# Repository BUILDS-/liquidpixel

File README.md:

# LiquidPixels

A project of [Christopher Woodall](http://www.cjwoodall.com) and 
[BUILDS](http://www.builds.cc).

## Rev. A Logs

- 4 proven working, 5 broked... Not 100% sure why, doesn't seem to be a soldering issue. I could have hooked them up wrong somehow during testing, but this should only apply to 1 or 2.
- Holes for .1" spaced headers are a little small, widen for future revisions.

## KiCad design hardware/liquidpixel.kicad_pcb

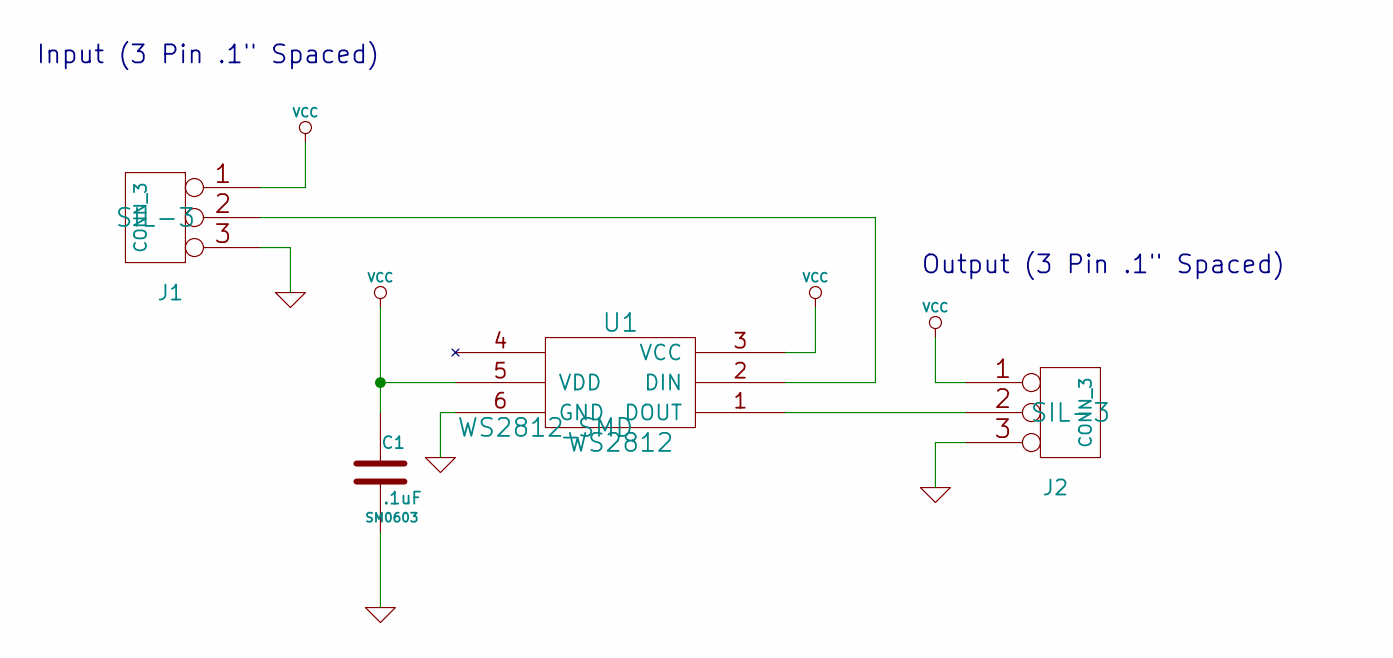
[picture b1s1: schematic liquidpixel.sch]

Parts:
C1: .1uF; SM0603
J1, J2: CONN_3; SIL-3
U1: WS2812; WS2812_SMD

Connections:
GND: C1.2, J1.3, J2.3, U1.6 (GND)
unnamed: J1.2 (PM), U1.2 (DIN)
unnamed: J2.2 (PM), U1.1 (DOUT)
VCC: C1.1, J1.1, J2.1, U1.3 (VCC), U1.5 (VDD)

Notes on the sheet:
Input (3 Pin .1" Spaced)
Output (3 Pin .1" Spaced)

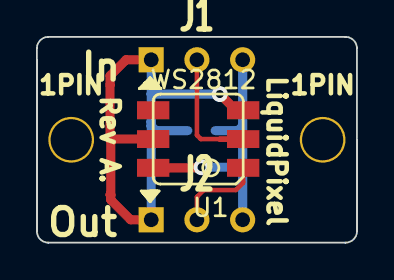
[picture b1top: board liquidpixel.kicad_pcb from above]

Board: 2 copper layers, 17.8 x 11.4 mm, 6 parts (1 on the bottom side), 4 nets.

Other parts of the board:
1PIN, 1PIN#2: P***; 1pin

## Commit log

2013-10-24 starting
2013-10-24 Added git ignore
2013-11-07 Added testing code for Arduino, and some logs from debugging
2013-11-07 log addition
2013-11-07 log addition... cleanup
